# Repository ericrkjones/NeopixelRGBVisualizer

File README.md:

# NeopixelRGBVisualizer
A Neopixel strand visualizer for an audio input that maps frequency distribution to color.  

# Modes
The device has multiple display modes.  To change modes, press the "M" button.

# Settings
To change the settings, press and hold the "M" button for 3 seconds.  The first light in the strand will change color to indicate the setting that will be adjusted.  Press the "M" button again to cycle to the next setting.  After cycling through all the setting modes, the settings will be stored for the next time you plug the device in.  

## Length
When the light is red, press the plus and minus buttons to change the length of the strand.  The strand is made of Neopixels, so it can be cut short (while the power is off) if you need it to be shorter.  To reset to the default 50 lights, press and hold both the plus and minus button at the same time.  

## Gain
When the light is green, press the plus and minus buttons to change the input gain.  Adjusting the gain up is possible but not recommended because the noise will be amplified.  Adjusting the noise down may be necessary.  If the appropriate gain cannot be set, external hardware may be required.  To reset to the default gain, press and hold both the plus and minus button at the same time.

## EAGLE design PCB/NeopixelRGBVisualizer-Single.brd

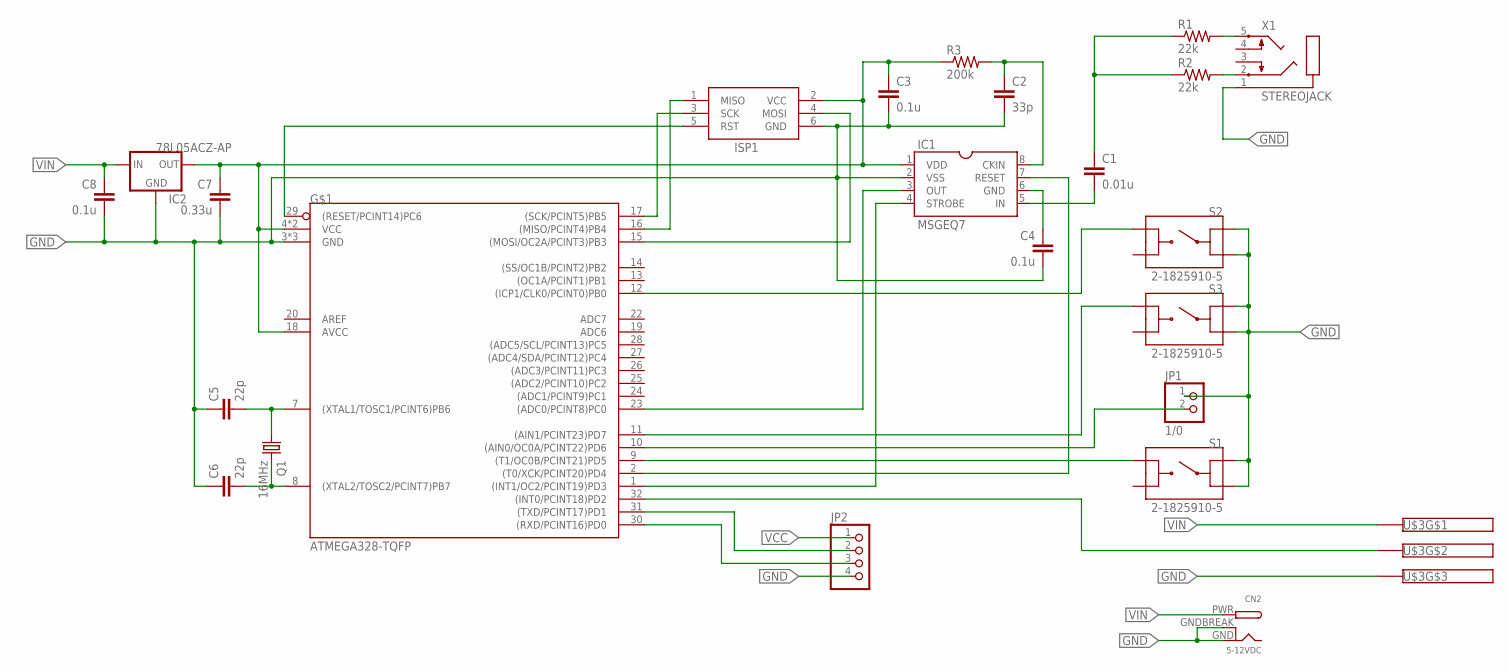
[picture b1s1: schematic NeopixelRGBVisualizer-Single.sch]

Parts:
C1: 0.01u; C0805
C2: 33p; C0805
C3, C4, C8: 0.1u; C0805
C5, C6: 22p; C0805
C7: 0.33u; C0805
CN2: 5-12VDC; DCJACK_2MM_PTH
IC1: MSGEQ7; DIL08
IC2: 78L05ACZ-AP; 78LXX
ISP1: AVRISP-6; AVRISP
JP1: 1/0; 1X02-ROUND
JP2: PINHD-1X4/OCT; 1X04-OCT
Q1: 16MHz; CTS406
R1, R2: 22k; M0805
R3: 200k; M0805
S1, S2, S3: 2-1825910-5; SW_2-1825910
U$1: ATMEGA328-TQFP; 32M1-A
U$3: 0039303035; 4.2MM-3PIN
X1: STEREOJACK; STX3100

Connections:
GND: C2.2, C3.2, C4.2, C5.1, C6.1, C7.2, C8.2, CN2.GND, CN2.GNDBREAK, IC1.2 (VSS), IC2.GND, ISP1.6 (GND), JP1.1, JP2.4, S1.1, S1.3, S2.1, S2.3, S3.1, S3.3, U$1.3 (GND), U$1.5 (GND), U$1.21 (GND), U$3.P$3, X1.1
MSGEQ7_OUT: IC1.3 (OUT), U$1.23 ((ADC0/PCINT8)PC0)
MSGEQ7_RESET: IC1.7 (RESET), U$1.2 ((T0/XCK/PCINT20)PD4)
MSGEQ7_STROBE: IC1.4 (STROBE), U$1.1 ((INT1/OC2/PCINT19)PD3)
unnamed: ISP1.3 (SCK), U$1.17 ((SCK/PCINT5)PB5)
unnamed: ISP1.5 (RST), U$1.29 ((RESET/PCINT14)PC6)
unnamed: ISP1.1 (MISO), U$1.16 ((MISO/PCINT4)PB4)
unnamed: ISP1.4 (MOSI), U$1.15 ((MOSI/OC2A/PCINT3)PB3)
unnamed: C4.1, IC1.6 (GND)
unnamed: S3.2, U$1.11 ((AIN1/PCINT23)PD7)
unnamed: C1.2, IC1.5 (IN)
unnamed: R2.2, X1.2
unnamed: C2.1, IC1.8 (CKIN), R3.2
unnamed: R1.2, X1.5
unnamed: C5.2, Q1.1, U$1.7 ((XTAL1/TOSC1/PCINT6)PB6)
unnamed: C6.2, Q1.3 (2), U$1.8 ((XTAL2/TOSC2/PCINT7)PB7)
unnamed: C1.1, R1.1, R2.1
unnamed: U$1.32 ((INT0/PCINT18)PD2), U$3.P$2
unnamed: S2.2, U$1.12 ((ICP1/CLK0/PCINT0)PB0)
unnamed: JP1.2, U$1.10 ((AIN0/OC0A/PCINT22)PD6)
unnamed: S1.2, U$1.9 ((T1/OC0B/PCINT21)PD5)
RX: JP2.3, U$1.30 ((RXD/PCINT16)PD0)
TX: JP2.2, U$1.31 ((TXD/PCINT17)PD1)
VCC: C3.1, C7.1, IC1.1 (VDD), IC2.OUT, ISP1.2 (VCC), JP2.1, R3.1, U$1.4 (VCC), U$1.6 (VCC), U$1.18 (AVCC)
VIN: C8.1, CN2.PWR, IC2.IN, U$3.P$1

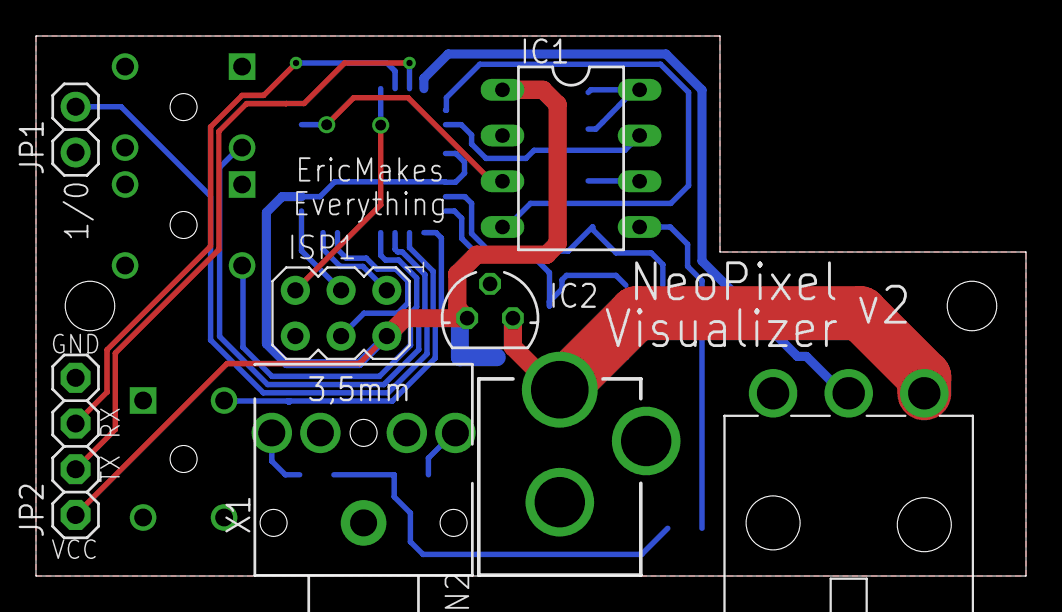
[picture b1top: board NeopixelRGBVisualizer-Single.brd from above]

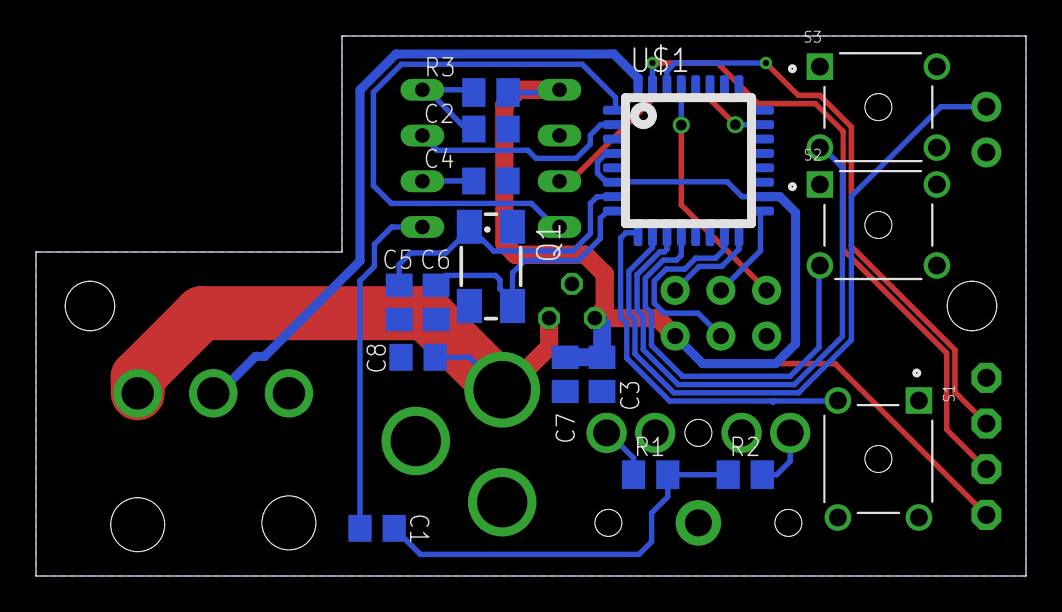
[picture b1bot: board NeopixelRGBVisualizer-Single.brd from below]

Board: 2 copper layers, 55.0 x 30.0 mm, 24 parts (16 on the bottom side), 25 nets.

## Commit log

2018-01-01 Created Arduino code.
2018-04-16 Eagle CAD for single-channel design.
2018-10-24 Version of board sent out for prototyping. Can connect with avrdude, having some other issues.
2018-10-31 Almost ready for second prototype order -Added 3 tactile buttons for control inputs: "Power","+","-" -Changed Phoenix screw terminal to Molex Mini-Fit Jr receptacle -Added small potentiometer as inpu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
2018-10-31 Reverted to first prototype, designing second prototype using updated libraries.
2018-11-01 Updated broken ATMega328PB footprint. This was caused by some Eagle glitch.
2018-11-01 Very tight design, needs to be fit into a larger enclosure.
2018-11-02 Reorganized and resized board to match new project box dimensions.
2018-11-04 Prototype version 2 with buttons and Molex minifit jr connector with shape appropriate for project boxes
2018-11-04 Partially completed silkscreen for v2 production
2018-11-05 Resized board to try to sqeeze it into the project box easier, made a cutout section for a big friendly panel-mount power button, and moved descriptive text from the tdocu layer to the tnames layer t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
2018-11-05 Updated Arduino code to work with Arduino core AVR board tools.
2018-11-20 Updated board to have correct footprints for tactile switches and potentiometer, since footprints acquired from SnapEDA were wrong.
2018-11-20 Created new branch starting with last good design. proto2 boards did not work for unknown reason. Tracking reason down now, but, due to time constraints, a new design will be created from the previou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
2018-11-21 Found problem in proto2 board to be caused by knockoff MSGEQ7 chip. Maintained fixed pinouts of tactile switches and removed potentiometer from board. Electrically, that circuit did not serve its pur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
2018-11-21 Added headers to access serial TX/RX pins, power, and GND. Requried 2 more vias.
2018-11-21 Moved Tx/Rx traces to increase clearance from pads.
2018-12-30 Added arduino code.
2023-12-17 removes unused variable
2023-12-17 adding ardunio documentation
2023-12-17 add repo for atmega328pb
